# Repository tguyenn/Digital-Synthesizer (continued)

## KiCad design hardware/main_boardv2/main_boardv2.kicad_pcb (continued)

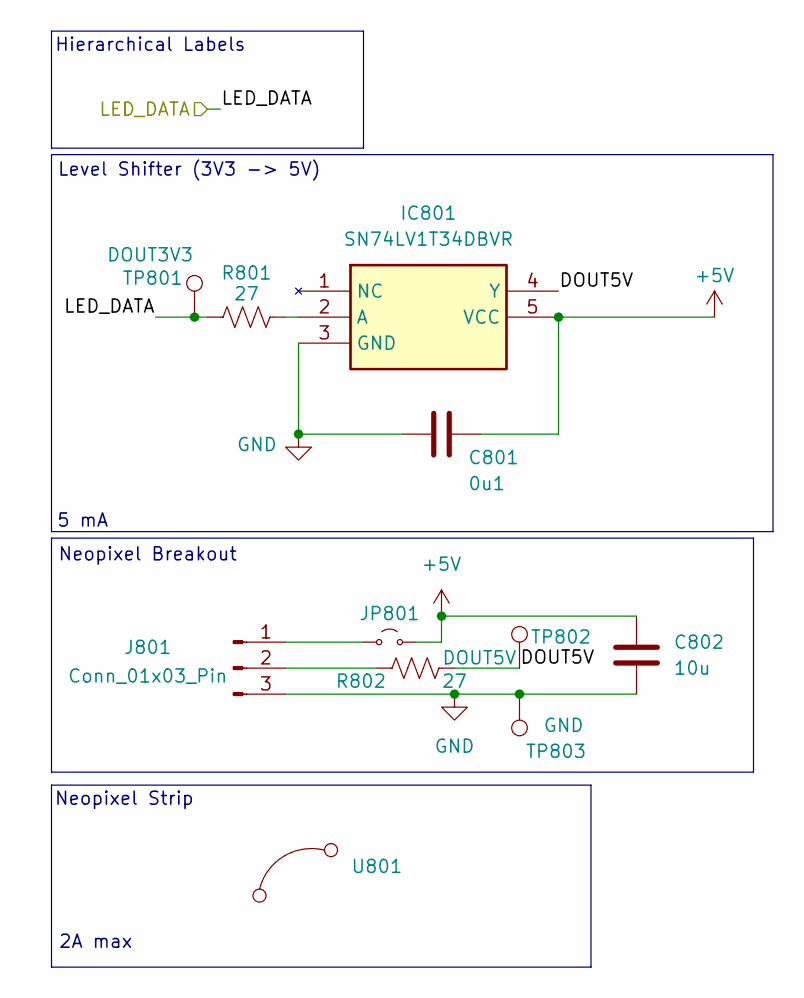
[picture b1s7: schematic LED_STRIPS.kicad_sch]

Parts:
C801: 0u1; C_0603_1608Metric
C802: 10u; C_0603_1608Metric
IC801: SN74LV1T34DBVR; SOT95P280X145-5N; Mouser Part Number 595-SN74LV1T34DBVR
J801: Conn_01x03_Pin; PinHeader_1x03_P2.54mm_Vertical
JP801: Jumper_2_Small_Bridged; SolderJumper-2_P1.3mm_Open_TrianglePad1.0x1.5mm
R801, R802: 27; R_0603_1608Metric
TP801: DOUT3V3; bettertestpoint2
TP802: DOUT5V; bettertestpoint2
TP803: GND; bettertestpoint2
U801: (no value)

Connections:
+5V: C801.2, C802.1, IC801.5 (VCC), JP801.2 (B); also elsewhere on the board
/LED Strip/DOUT5V: IC801.4 (Y), R802.2, TP802.1
/LED Strip/LED_DATA: R801.1, TP801.1; also elsewhere on the board
GND: C801.1, C802.2, IC801.3 (GND), J801.3, TP803.1; also elsewhere on the board
unnamed: IC801.2 (A), R801.2
unnamed: J801.1, JP801.1 (A)
unnamed: J801.2, R802.1

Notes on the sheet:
Neopixel Breakout
5 mA
Neopixel Strip
2A max
Hierarchical Labels
Level Shifter (3V3 -> 5V)

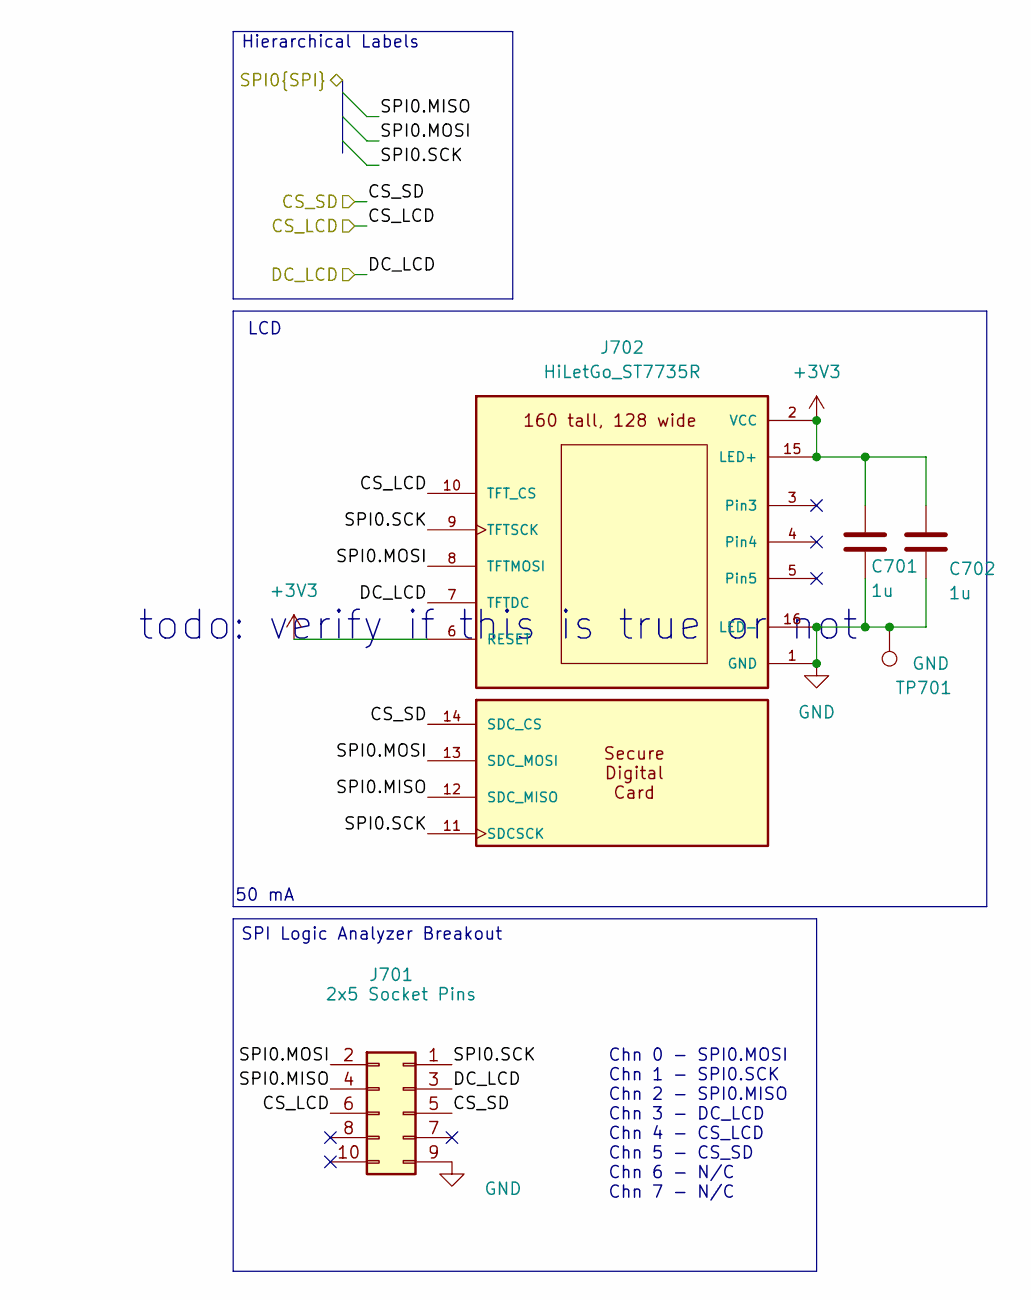
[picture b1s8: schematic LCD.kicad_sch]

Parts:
C701, C702: 1u; C_0603_1608Metric
J701: 2x5 Socket Pins; logic_analyzer_slot_2x5_2.54mm
J702: HiLetGo_ST7735R; hiletgo_st7735r
TP701: GND; bettertestpoint2

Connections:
+3V3: C701.1, C702.1, J702.2 (VCC), J702.6 (RESET), J702.15 (LED+); also elsewhere on the board
/LCD/CS_LCD: J701.6, J702.10 (TFT_CS); also elsewhere on the board
/LCD/CS_SD: J701.5, J702.14 (SDC_CS); also elsewhere on the board
/LCD/DC_LCD: J701.3, J702.7 (TFTDC); also elsewhere on the board
/LCD/SPI0.MISO: J701.4, J702.12 (SDC_MISO); also elsewhere on the board
/LCD/SPI0.MOSI: J701.2, J702.8 (TFTMOSI), J702.13 (SDC_MOSI); also elsewhere on the board
/LCD/SPI0.SCK: J701.1, J702.9 (TFTSCK), J702.11 (SDCSCK); also elsewhere on the board
GND: C701.2, C702.2, J701.9, J702.1 (GND), J702.16 (LED-), TP701.1; also elsewhere on the board

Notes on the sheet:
todo: verify if this is true or not
LCD
SPI Logic Analyzer Breakout
50 mA
Hierarchical Labels
Chn 0 - SPI0.MOSI Chn 1 - SPI0.SCK Chn 2 - SPI0.MISO Chn 3 - DC_LCD Chn 4 - CS_LCD Chn 5 - CS_SD Chn 6 - N/C Chn 7 - N/C

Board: 2 copper layers, 121 parts (0 on the bottom side), 85 nets, no tracks yet.

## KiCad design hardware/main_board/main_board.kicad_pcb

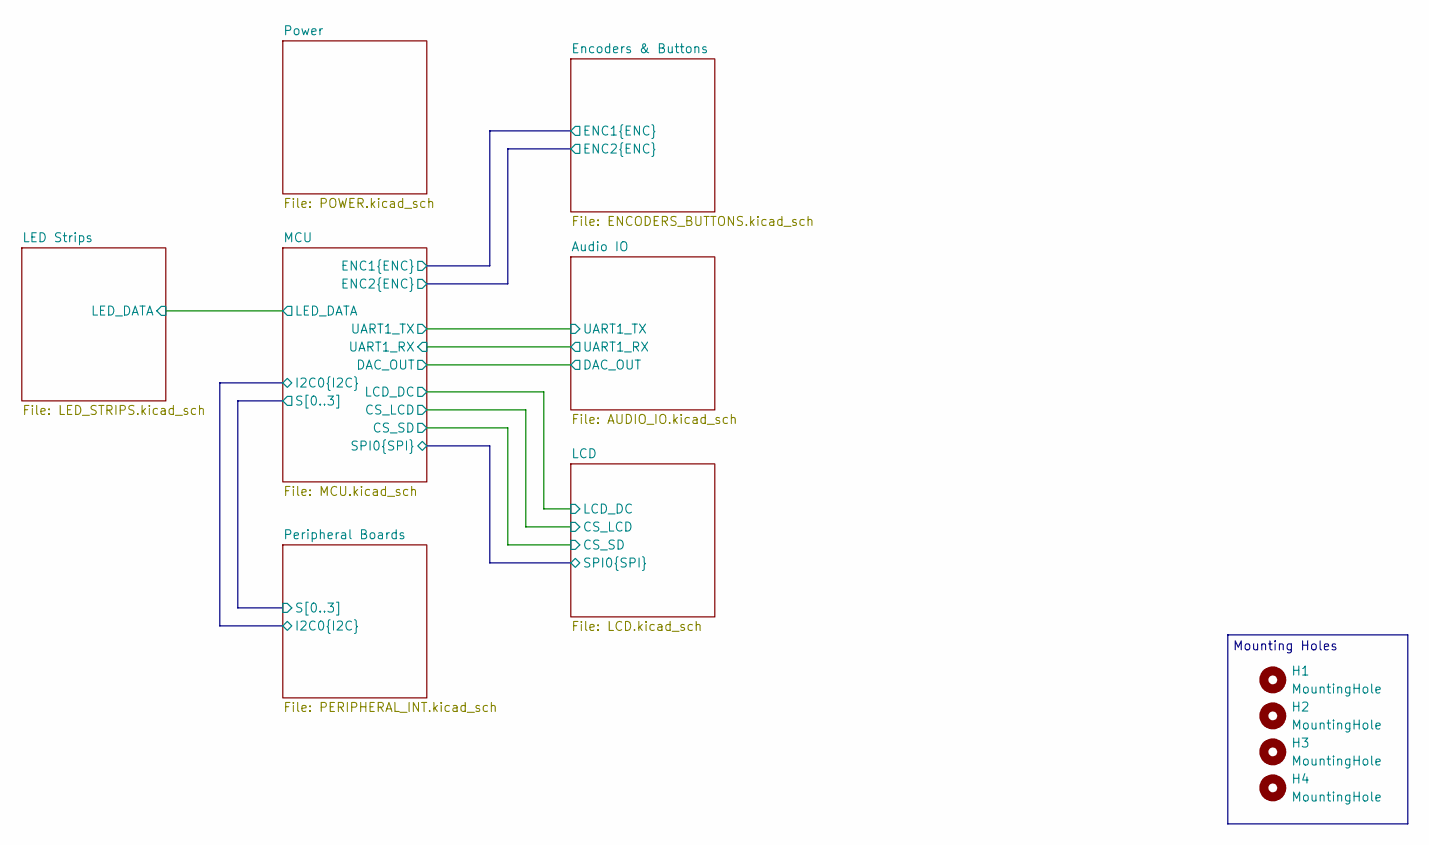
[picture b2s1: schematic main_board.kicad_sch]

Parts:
H1, H2, H3, H4: MountingHole; MountingHole_3.2mm_M3

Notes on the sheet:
Mounting Holes

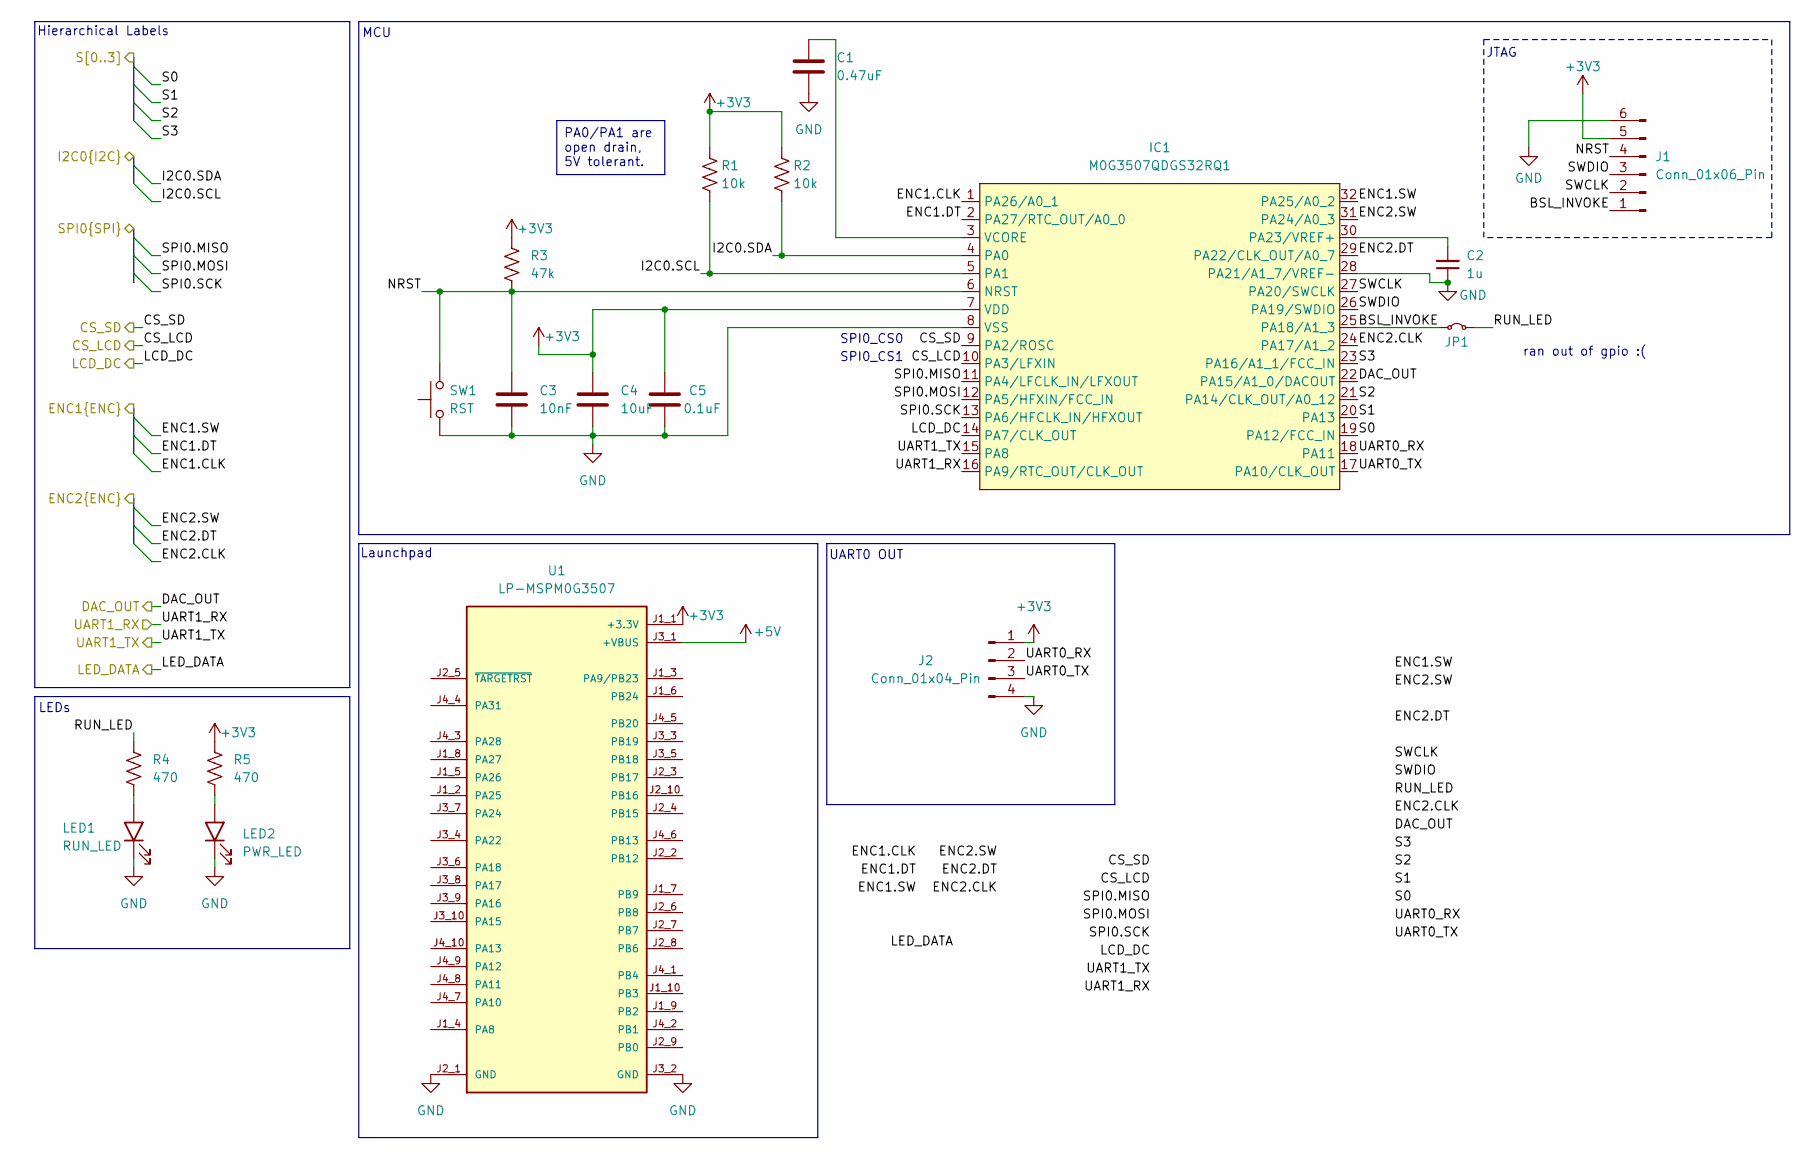
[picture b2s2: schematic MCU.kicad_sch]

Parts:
C1: 0.47uF; C_0805_2012Metric
C2: 1u; C_0805_2012Metric
C3: 10nF; C_0805_2012Metric
C4: 10uF; C_0805_2012Metric
C5: 0.1uF; C_0805_2012Metric
IC1: M0G3507QDGS32RQ1; generic_VSSOP_0.5mm
J1: Conn_01x06_Pin; PinHeader_1x06_P2.54mm_Vertical
J2: Conn_01x04_Pin; PinHeader_1x05_P2.54mm_Vertical
JP1: Jumper_2_Small_Bridged
LED1: RUN_LED; LEDC2012X40N; Mouser Part Number 720-LSR976-NR-1
LED2: PWR_LED; LEDC2012X40N; Mouser Part Number 720-LSR976-NR-1
R1, R2: 10k; R_0805_2012Metric
R3: 47k; R_0805_2012Metric
R4, R5: 470; R_0805_2012Metric
SW1: RST; SW_PUSH_6mm
U1: LP-MSPM0G3507; ti_LP_MSPM0G3507

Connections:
+3V3: C4.1, C5.1, IC1.7 (VDD), J1.5, J2.1, R1.2, R2.2, R3.1, R5.1, U1.J1_1 (+3.3V); also elsewhere on the board
+5V: U1.J3_1 (+VBUS); also elsewhere on the board
/Audio IO/DAC_OUT: IC1.22 (PA15/A1_0/DACOUT); also elsewhere on the board
/Audio IO/UART1_RX: IC1.16 (PA9/RTC_OUT/CLK_OUT); also elsewhere on the board
/Audio IO/UART1_TX: IC1.15 (PA8); also elsewhere on the board
/Encoders & Buttons/ENC1.CLK: IC1.1 (PA26/A0_1); also elsewhere on the board
/Encoders & Buttons/ENC1.DT: IC1.2 (PA27/RTC_OUT/A0_0); also elsewhere on the board
/Encoders & Buttons/ENC1.SW: IC1.32 (PA25/A0_2); also elsewhere on the board
/Encoders & Buttons/ENC2.CLK: IC1.24 (PA17/A1_2); also elsewhere on the board
/Encoders & Buttons/ENC2.DT: IC1.29 (PA22/CLK_OUT/A0_7); also elsewhere on the board
/Encoders & Buttons/ENC2.SW: IC1.31 (PA24/A0_3); also elsewhere on the board
/LCD/CS_LCD: IC1.10 (PA3/LFXIN); also elsewhere on the board
/LCD/CS_SD: IC1.9 (PA2/ROSC); also elsewhere on the board
/LCD/LCD_DC: IC1.14 (PA7/CLK_OUT); also elsewhere on the board
/LCD/SPI0.MISO: IC1.11 (PA4/LFCLK_IN/LFXOUT); also elsewhere on the board
/LCD/SPI0.MOSI: IC1.12 (PA5/HFXIN/FCC_IN); also elsewhere on the board
/LCD/SPI0.SCK: IC1.13 (PA6/HFCLK_IN/HFXOUT); also elsewhere on the board
/MCU/BSL_INVOKE: IC1.25 (PA18/A1_3), J1.1, JP1.1 (A)
/MCU/I2C0.SCL: IC1.5 (PA1), R1.1; also elsewhere on the board
/MCU/I2C0.SDA: IC1.4 (PA0), R2.1; also elsewhere on the board
/MCU/NRST: C3.1, IC1.6 (NRST), J1.4, R3.2, SW1.2
/MCU/RUN_LED: JP1.2 (B), R4.1
/MCU/S0: IC1.19 (PA12/FCC_IN); also elsewhere on the board
/MCU/S1: IC1.20 (PA13); also elsewhere on the board
/MCU/S2: IC1.21 (PA14/CLK_OUT/A0_12); also elsewhere on the board
/MCU/S3: IC1.23 (PA16/A1_1/FCC_IN); also elsewhere on the board
/MCU/SWCLK: IC1.27 (PA20/SWCLK), J1.2
/MCU/SWDIO: IC1.26 (PA19/SWDIO), J1.3
/MCU/UART0_RX: IC1.18 (PA11), J2.2
/MCU/UART0_TX: IC1.17 (PA10/CLK_OUT), J2.3
GND: C1.2, C2.1, C3.2, C4.2, C5.2, IC1.8 (VSS), IC1.28 (PA21/A1_7/VREF-), J1.6, J2.4, LED1.1 (K), LED2.1 (K), SW1.1, U1.J2_1 (GND), U1.J3_2 (GND); also elsewhere on the board
unnamed: C2.2, IC1.30 (PA23/VREF+)
unnamed: C1.1, IC1.3 (VCORE)
unnamed: LED1.2 (A), R4.2
unnamed: LED2.2 (A), R5.2

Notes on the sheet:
MCU
LEDs
UART0 OUT
Launchpad
SPI0_CS1
Hierarchical Labels
SPI0_CS0
ran out of gpio :(
JTAG
PA0/PA1 are open drain, 5V tolerant.

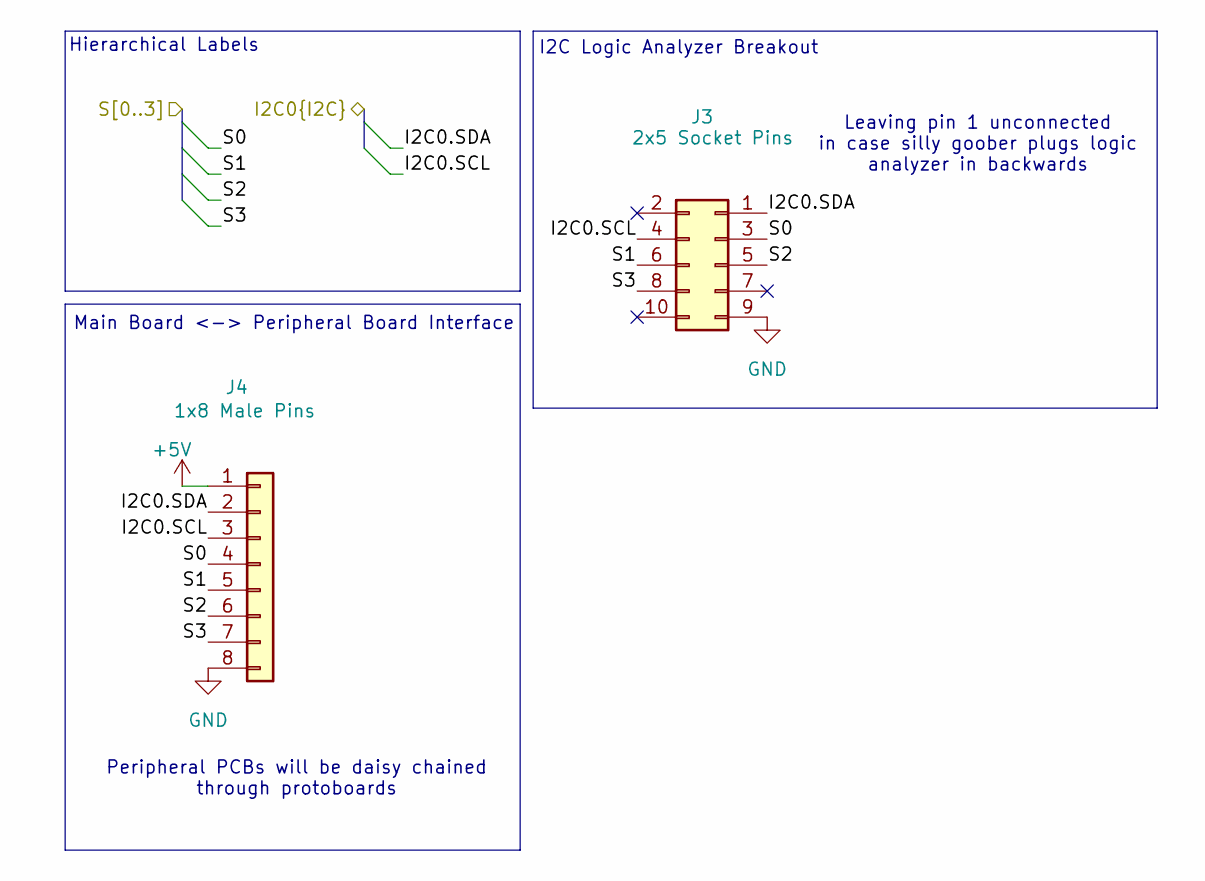
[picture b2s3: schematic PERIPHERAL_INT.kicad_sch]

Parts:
J3: 2x5 Socket Pins; logic_analyzer_slot_2x5_2.54mm
J4: 1x8 Male Pins; PinSocket_1x08_P2.54mm_Vertical

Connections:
+5V: J4.1; also elsewhere on the board
/MCU/I2C0.SCL: J3.4, J4.3; also elsewhere on the board
/MCU/I2C0.SDA: J3.1, J4.2; also elsewhere on the board
/MCU/S0: J3.3, J4.4; also elsewhere on the board
/MCU/S1: J3.6, J4.5; also elsewhere on the board
/MCU/S2: J3.5, J4.6; also elsewhere on the board
/MCU/S3: J3.8, J4.7; also elsewhere on the board
GND: J3.9, J4.8; also elsewhere on the board

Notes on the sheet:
Hierarchical Labels
Peripheral PCBs will be daisy chained through protoboards
Leaving pin 1 unconnected in case silly goober plugs logic analyzer in backwards
Main Board <-> Peripheral Board Interface
I2C Logic Analyzer Breakout

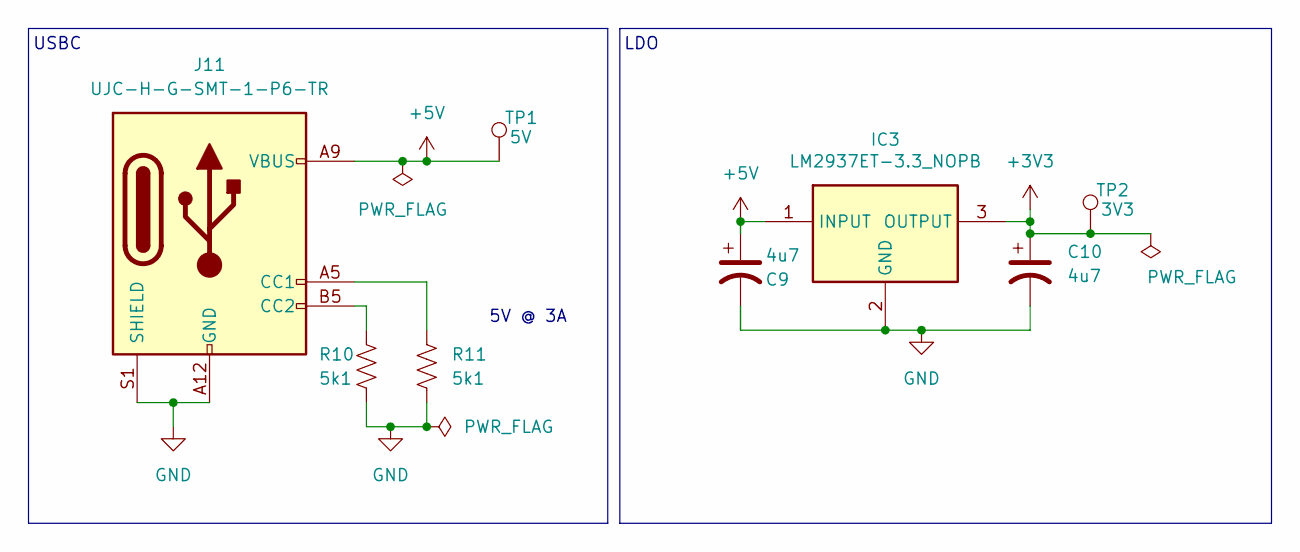
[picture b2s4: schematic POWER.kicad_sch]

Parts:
C9, C10: 4u7; CP_Radial_Tantal200mil
IC3: LM2937ET-3.3_NOPB; TO254P470X1028X1955-3P; Mouser Part Number 926-LM2937ET-3.3NOPB
J11: UJC-H-G-SMT-1-P6-TR; UJCHGSMT1P6TR; Manufacturer_Part_Number UJC-H-G-SMT-1-P6-TR
R10, R11: 5k1; R_0805_2012Metric
TP1: 5V; bettertestpoint2
TP2: 3V3; bettertestpoint2

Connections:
+3V3: C10.1, IC3.3 (OUTPUT), TP2.1; also elsewhere on the board
+5V: C9.1, IC3.1 (INPUT), J11.A9 (VBUS), J11.B9 (VBUS), TP1.1; also elsewhere on the board
GND: C9.2, C10.2, IC3.2 (GND), J11.A12 (GND), J11.B12 (GND), J11.S1 (SHIELD), R10.2, R11.2; also elsewhere on the board
unnamed: J11.A5 (CC1), R11.1
unnamed: J11.B5 (CC2), R10.1

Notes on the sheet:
USBC
LDO
5V @ 3A

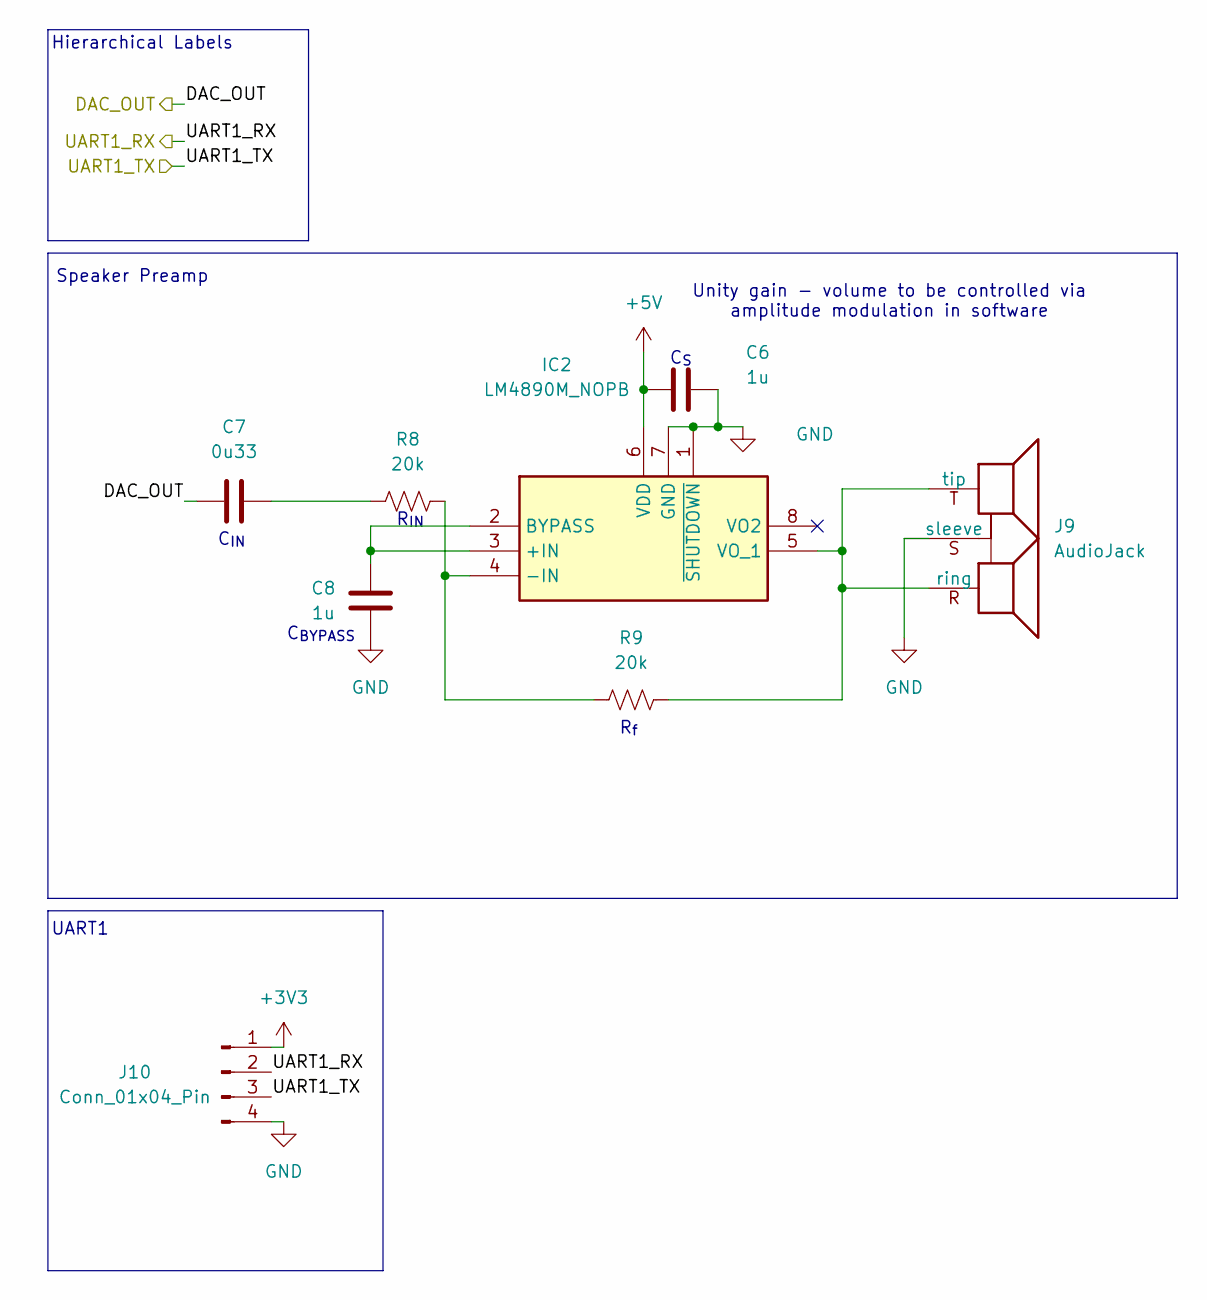
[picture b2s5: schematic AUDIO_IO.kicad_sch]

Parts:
C6, C8: 1u; C_0805_2012Metric
C7: 0u33; C_0805_2012Metric
IC2: LM4890M_NOPB; ti_LM4890M_NOPB; Mouser Part Number 926-LM4890M/NOPB
J9: AudioJack; Jack_3.5mm_CUI_SJ1-3523N_Horizontal
J10: Conn_01x04_Pin; PinHeader_1x05_P2.54mm_Vertical
R8, R9: 20k; R_0805_2012Metric

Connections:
+3V3: J10.1; also elsewhere on the board
+5V: C6.2, IC2.6 (VDD); also elsewhere on the board
/Audio IO/DAC_OUT: C7.1; also elsewhere on the board
/Audio IO/UART1_RX: J10.2; also elsewhere on the board
/Audio IO/UART1_TX: J10.3; also elsewhere on the board
GND: C6.1, C8.2, IC2.1 (~SHUTDOWN), IC2.7 (GND), J9.S (sleeve), J10.4; also elsewhere on the board
unnamed: C7.2, R8.1
unnamed: C8.1, IC2.2 (BYPASS), IC2.3 (+IN)
unnamed: IC2.4 (-IN), R8.2, R9.1
unnamed: IC2.5 (VO_1), J9.R (ring), J9.T (tip), R9.2

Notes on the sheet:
Unity gain - volume to be controlled via amplitude modulation in software
Speaker Preamp
UART1
R_{f}
C_{BYPASS}
R_{IN}
C_{S}
C_{IN}
Hierarchical Labels

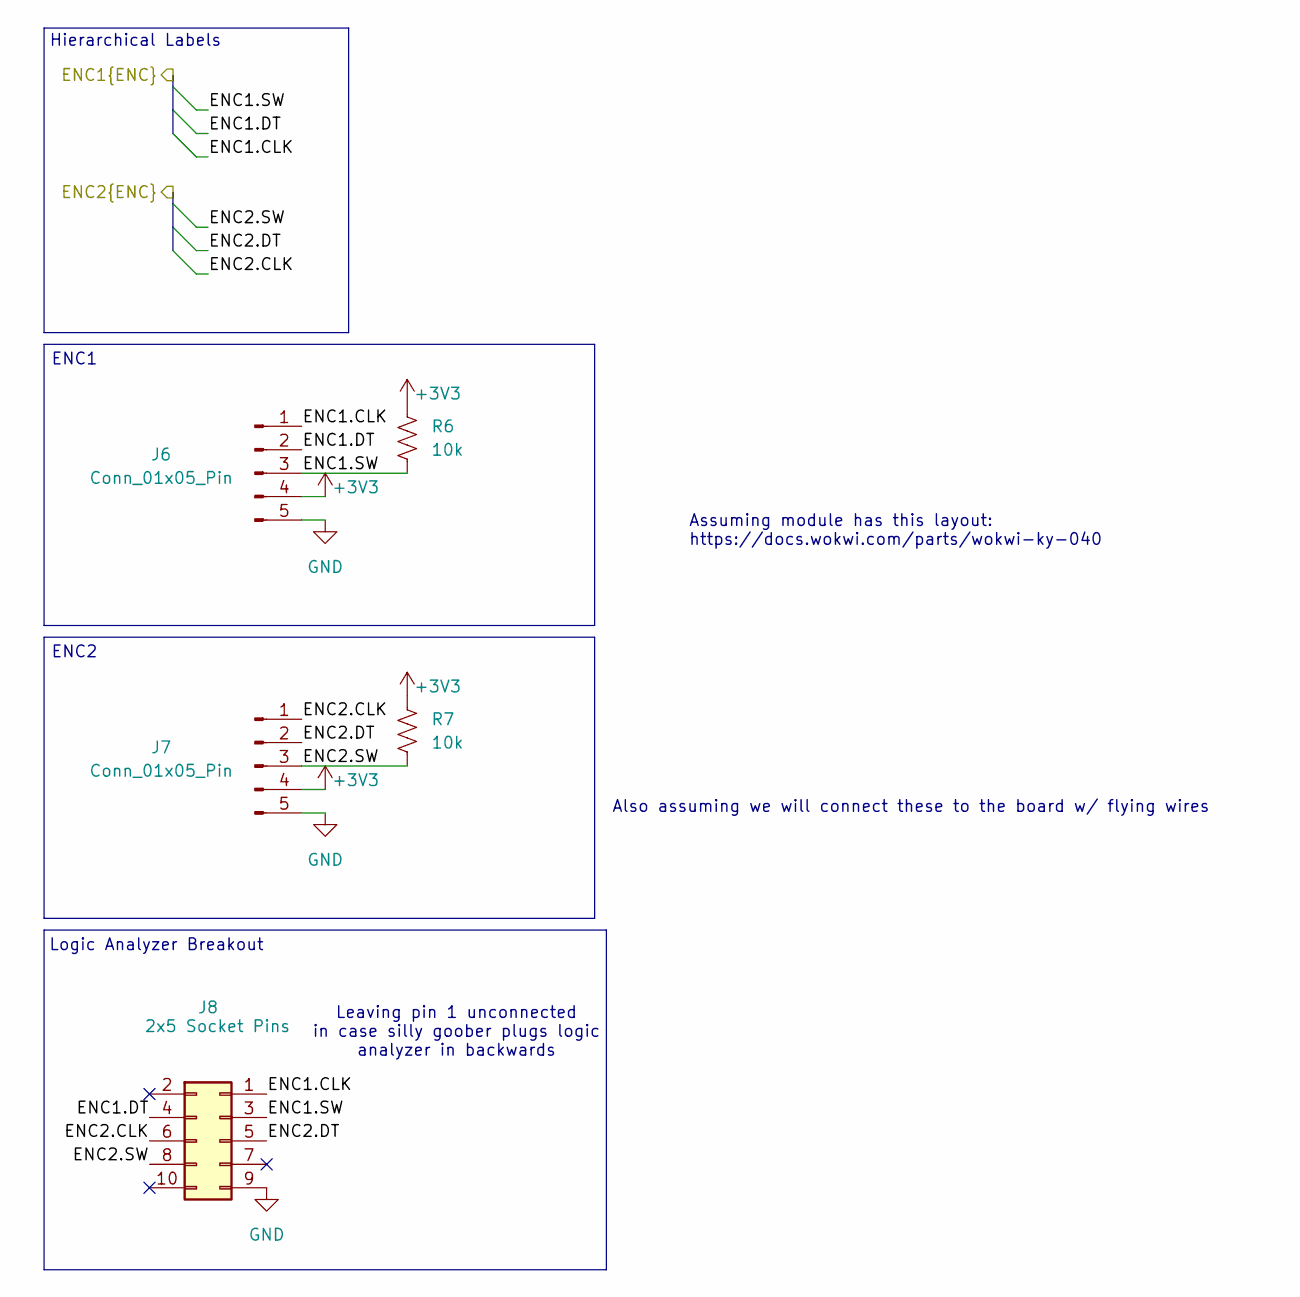
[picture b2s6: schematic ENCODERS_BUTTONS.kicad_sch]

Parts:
J6, J7: Conn_01x05_Pin; PinHeader_1x05_P2.54mm_Vertical
J8: 2x5 Socket Pins; logic_analyzer_slot_2x5_2.54mm
R6, R7: 10k; R_0805_2012Metric

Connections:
+3V3: J6.4, J7.4, R6.2, R7.2; also elsewhere on the board
/Encoders & Buttons/ENC1.CLK: J6.1, J8.1; also elsewhere on the board
/Encoders & Buttons/ENC1.DT: J6.2, J8.4; also elsewhere on the board
/Encoders & Buttons/ENC1.SW: J6.3, J8.3, R6.1; also elsewhere on the board
/Encoders & Buttons/ENC2.CLK: J7.1, J8.6; also elsewhere on the board
/Encoders & Buttons/ENC2.DT: J7.2, J8.5; also elsewhere on the board
/Encoders & Buttons/ENC2.SW: J7.3, J8.8, R7.1; also elsewhere on the board
GND: J6.5, J7.5, J8.9; also elsewhere on the board

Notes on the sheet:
Also assuming we will connect these to the board w/ flying wires
Logic Analyzer Breakout
ENC1
ENC2
Leaving pin 1 unconnected in case silly goober plugs logic analyzer in backwards
Hierarchical Labels
Assuming module has this layout: https://docs.wokwi.com/parts/wokwi-ky-040

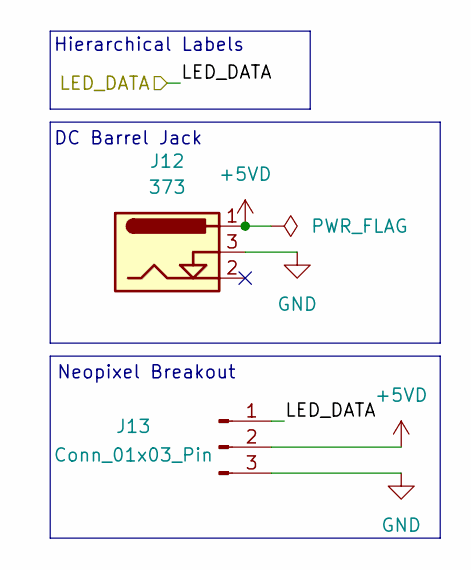
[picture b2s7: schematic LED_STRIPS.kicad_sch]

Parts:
J12: 373; Mouser Part Number 485-373
J13: Conn_01x03_Pin; PinHeader_1x03_P2.54mm_Vertical

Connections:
+5VD: J12.1, J13.2
/LED Strips/LED_DATA: J13.1
GND: J12.3, J13.3; also elsewhere on the board

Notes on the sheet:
Neopixel Breakout
DC Barrel Jack
Hierarchical Labels

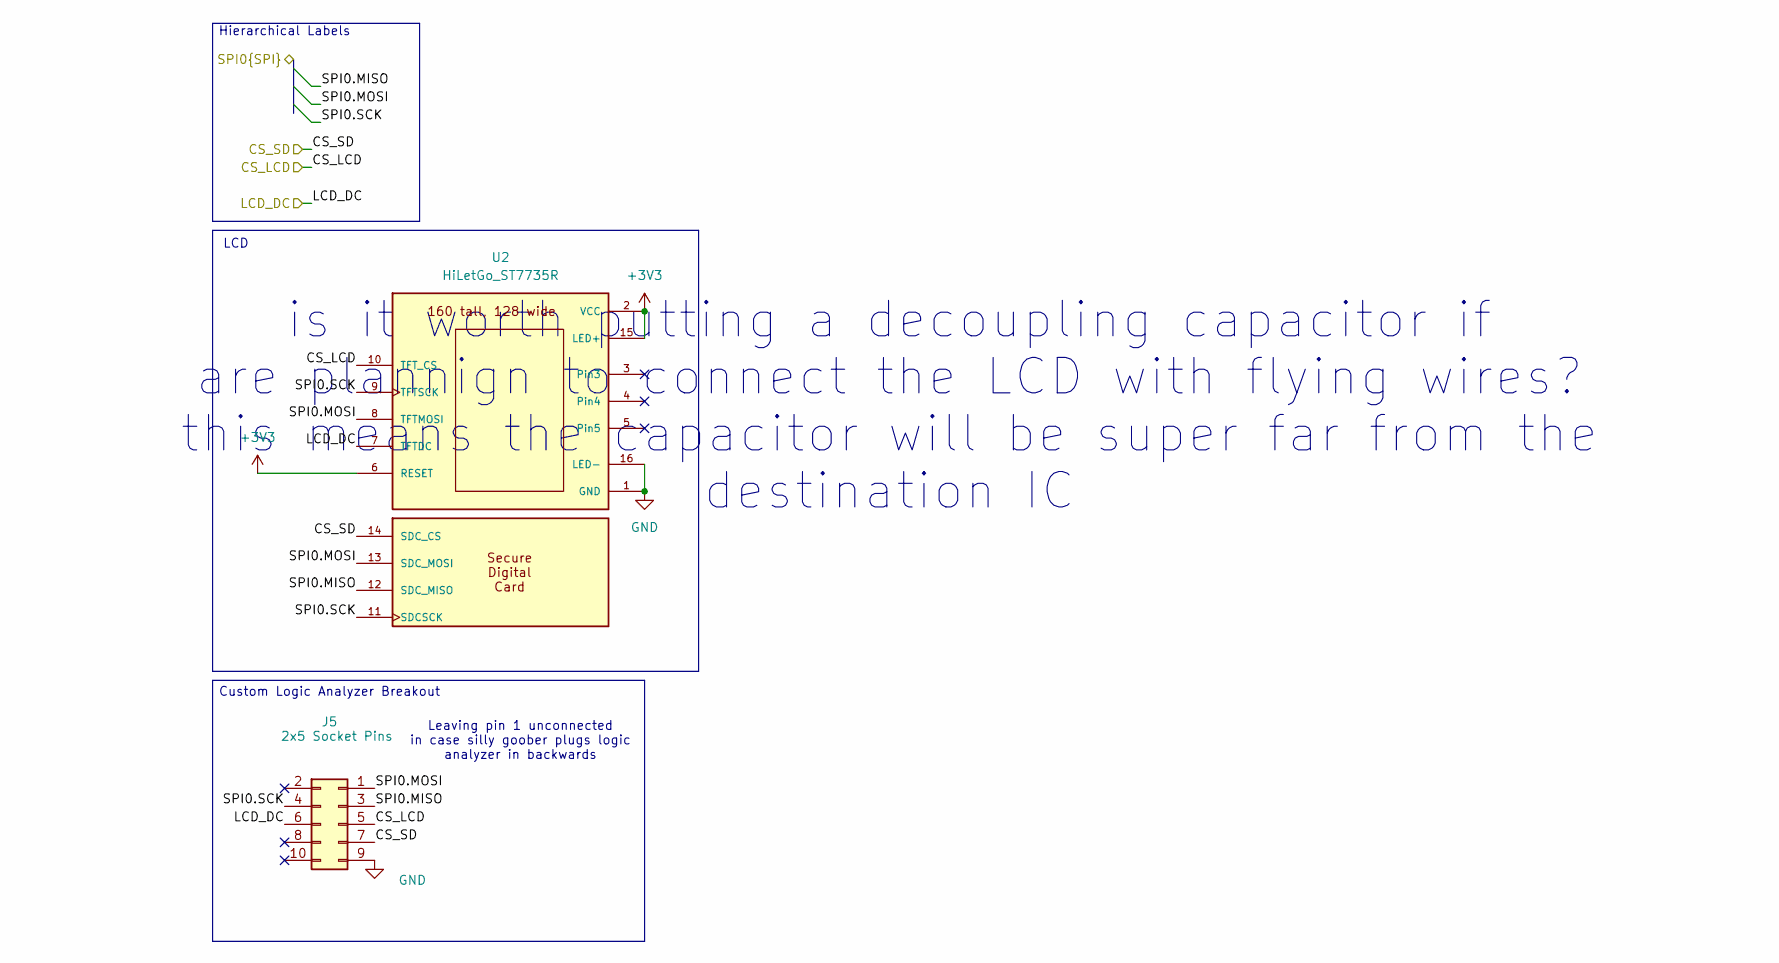
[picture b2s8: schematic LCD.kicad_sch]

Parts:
J5: 2x5 Socket Pins; logic_analyzer_slot_2x5_2.54mm
U2: HiLetGo_ST7735R; hiletgo_st7735r

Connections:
+3V3: U2.2 (VCC), U2.6 (RESET), U2.15 (LED+); also elsewhere on the board
/LCD/CS_LCD: J5.5, U2.10 (TFT_CS); also elsewhere on the board
/LCD/CS_SD: J5.7, U2.14 (SDC_CS); also elsewhere on the board
/LCD/LCD_DC: J5.6, U2.7 (TFTDC); also elsewhere on the board
/LCD/SPI0.MISO: J5.3, U2.12 (SDC_MISO); also elsewhere on the board
/LCD/SPI0.MOSI: J5.1, U2.8 (TFTMOSI), U2.13 (SDC_MOSI); also elsewhere on the board
/LCD/SPI0.SCK: J5.4, U2.9 (TFTSCK), U2.11 (SDCSCK); also elsewhere on the board
GND: J5.9, U2.1 (GND), U2.16 (LED-); also elsewhere on the board

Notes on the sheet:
LCD
Custom Logic Analyzer Breakout
Hierarchical Labels
Leaving pin 1 unconnected in case silly goober plugs logic analyzer in backwards
is it worth putting a decoupling capacitor if are plannign to connect the LCD with flying wires? this means the capacitor will be super far from the destination IC

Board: 2 copper layers, 48 parts (0 on the bottom side), 41 nets, no tracks yet.

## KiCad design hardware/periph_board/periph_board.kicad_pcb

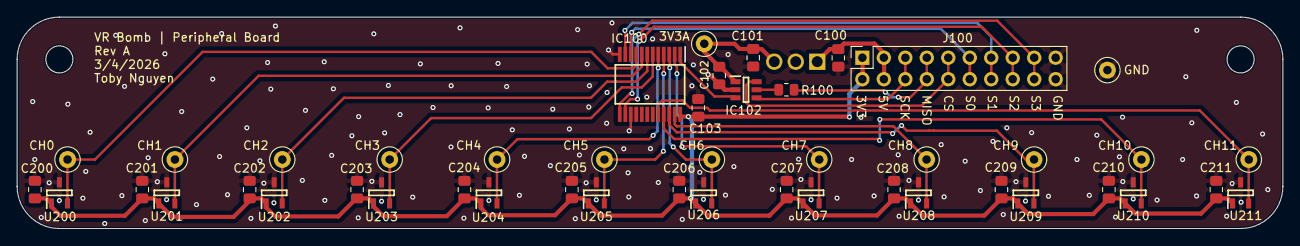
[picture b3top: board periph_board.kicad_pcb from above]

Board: 2 copper layers, 149.7 x 25.0 mm, 49 parts (1 on the bottom side), 25 nets.

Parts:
C100, C101, C102, C103, C200, C201, C202, C203, C204, C205, C206, C207, C208, C209, C210, C211: 1u; C_0805_2012Metric_Pad1.18x1.45mm_HandSolder
H100, H101: MountingHole; MountingHole_3.2mm_M3
IC100: CD74HC4067SM96; SOP65P780X200-24N
IC101: LM2937ET-3.3_NOPB; TO254P470X1028X1955-3P
IC102: ADC121S021CIMFX_NOPB; SOT95P280X145-6N
J100: 2x10 Male Pins; PinSocket_2x10_P2.54mm_Vertical
R100: 100; R_0805_2012Metric
TP100: CH0; bettertestpoint2
TP102: CH1; bettertestpoint2
TP103: 3V3A; bettertestpoint2
TP105: CH2; bettertestpoint2
TP106: CH3; bettertestpoint2
TP107: CH4; bettertestpoint2
TP108: CH5; bettertestpoint2
TP109: CH6; bettertestpoint2
TP110: GND; bettertestpoint2
TP111: CH7; bettertestpoint2
TP112: CH8; bettertestpoint2
TP113: CH9; bettertestpoint2
TP114: CH10; bettertestpoint2
TP115: CH11; bettertestpoint2
U200, U201, U202, U203, U204, U205, U206, U207, U208, U209, U210, U211: AH49HNTR-G1; SOT95P282X145-3N

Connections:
+3.3VADC: C101.2, C102.2, IC101.3 (OUTPUT), IC102.1 (VA), TP103.1
+3V3: C103.2, C200.2, C201.2, C202.2, C203.2, C204.2, C205.2, C206.2, C207.2, C208.2, C209.2, C210.2, C211.2, IC100.24 (VCC), J100.1, J100.2, U200.1 (VCC), U201.1 (VCC), U202.1 (VCC), U203.1 (VCC), U204.1 (VCC), U205.1 (VCC), U206.1 (VCC), U207.1 (VCC), U208.1 (VCC), U209.1 (VCC), U210.1 (VCC), U211.1 (VCC)
+5V: C100.2, IC101.1 (INPUT), J100.3, J100.4
/CH0: IC100.9 (I0), TP100.1, U200.2 (OUT)
/CH1: IC100.8 (I1), TP102.1, U201.2 (OUT)
/CH2: IC100.7 (I2), TP105.1, U202.2 (OUT)
/CH3: IC100.6 (I3), TP106.1, U203.2 (OUT)
/CH4: IC100.5 (I4), TP107.1, U204.2 (OUT)
/CH5: IC100.4 (I5), TP108.1, U205.2 (OUT)
/CH6: IC100.3 (I6), TP109.1, U206.2 (OUT)
/CH7: IC100.2 (I7), TP111.1, U207.2 (OUT)
/CH8: IC100.23 (I8), TP112.1, U208.2 (OUT)
/CH9: IC100.22 (I9), TP113.1, U209.2 (OUT)
/CH10: IC100.21 (I10), TP114.1, U210.2 (OUT)
/CH11: IC100.20 (I11), TP115.1, U211.2 (OUT)
/CS: IC102.6 (CS), J100.9, J100.10
/HALL_OUT: IC100.1 (COMMON_INPUT/OUTPUT), IC102.3 (VIN)
/MISO: J100.7, J100.8, R100.2
/S0: IC100.10 (S0), J100.11, J100.12
/S1: IC100.11 (S1), J100.13, J100.14
/S2: IC100.14 (S2), J100.15, J100.16
/S3: IC100.13 (S3), J100.17, J100.18
/SCK: IC102.4 (SCLK), J100.5, J100.6
GND: C100.1, C101.1, C102.1, C103.1, C200.1, C201.1, C202.1, C203.1, C204.1, C205.1, C206.1, C207.1, C208.1, C209.1, C210.1, C211.1, IC100.12 (GND), IC100.15 (~E), IC101.2 (GND), IC102.2 (GND), J100.19, J100.20, TP110.1, U200.3 (GND), U201.3 (GND), U202.3 (GND), U203.3 (GND), U204.3 (GND), U205.3 (GND), U206.3 (GND), U207.3 (GND), U208.3 (GND), U209.3 (GND), U210.3 (GND), U211.3 (GND)
unnamed: IC102.5 (SDATA), R100.1

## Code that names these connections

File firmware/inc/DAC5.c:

/* DAC5.c
 * Students put your names here
 * Modified: put date here
 * 5-bit binary-weighted DAC connected to PB4-PB0
 */
#include <ti/devices/msp/msp.h>
#define PB0INDEX  11 // UART0_TX  SPI1_CS2  TIMA1_C0  TIMA0_C2
#define PB1INDEX  12 // UART0_RX  SPI1_CS3  TIMA1_C1  TIMA0_C2N
#define PB2INDEX  14 // UART3_TX  UART2_CTS I2C1_SCL  TIMA0_C3  UART1_CTS TIMG6_C0  TIMA1_C0
#define PB3INDEX  15 // UART3_RX  UART2_RTS I2C1_SDA  TIMA0_C3N UART1_RTS TIMG6_C1  TIMA1_C1
#define PB4INDEX  16 // UART1_TX  UART3_CTS TIMA1_C0  TIMA0_C2  TIMA1_C0N

// **************DAC5_Init*********************
// Initialize 5-bit DAC, called once
// Input: none
// Output: none
void DAC5_Init(void){
// Assumes LaunchPad_Init has been called
// I.e., PortB has already been reset and activated (do not reset PortB here again)
     // write this
}

// **************DAC5_Out*********************
// output to DAC5
// Input: 5-bit data, 0 to 31
// Input=n is converted to n*3.3V/31
// Output: none
// Note: this solution must be friendly
void DAC5_Out(uint32_t data){
     // write this
}

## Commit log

2026-02-28 Flatten
2026-03-03 added drawio file. added samacsys config for both kicad projects
2026-03-03 sw gitignore
2026-03-04 Finished Rev A of peripheral PCB schematic/layout (need to find values for resistors lol). Added ECE445L lab docs
2026-03-05 layout with bad adc
2026-03-06 MSPM0 Starter
2026-03-07 ece445l libraries added. moved mspm0 starter to /hw to /hardware with other files
2026-03-07 third peripheral board layout done
2026-03-07 replaced LDO thing to be free one in lab checkout. added some stuff to main board (wip)
2026-03-08 finished periph board rev A. ready for order! added some more content to main board
2026-03-13 pls review pboard with i2c sensor
2026-03-17 Fixed DRC errors
2026-03-17 Created gerbers using kicad-jlcpcb-tools
2026-03-23 added 319k lab 7 to resources
2026-03-23 please
2026-03-23 fixed peripheral board dimensions to be compatible with 2.54 mm pitch protoboard for daisy chaining. deleted gerbers. added some more content to main board (wip)
2026-03-23 Jeffey try building this
2026-03-25 reorganize lol
2026-03-26 added lakshay suggestions to peripheral board. removed bypass jumper from main board audio amp. added led strip interface. added too many things to remember i forgor
2026-03-27 main board stuff. removed usbc for power. added level shifter for led logic signal. added lights for mux select signals. finished layout + pass DRC
2026-03-27 removed starter msp proj. fixed all 3d model paths (hopefully). added power led and changed MH to be 319k standoff compatible
2026-03-27 added requirements doc
2026-03-28 pcb review changes
2026-03-30 added selection line LEDs to p board
2026-03-30 Dimensioned correctly, need to reroute for hall effects
2026-03-30 Rerouted for adjusted key offsets
2026-03-31 changed level shifter. bunch of aesthetic changes. led resistors changed on main board. saving before nuke mouser.co.uk
2026-03-31 finished everything except bom information. drc verification
2026-03-31 fuck shit
2026-04-03 updated requirements doc
2026-04-09 led info
2026-04-09 up to date scheamtic
2026-04-14 build and flash blinky to launchpad in mainboard project dir
2026-04-16 led chaser launchpad select lines
2026-04-17 rip morris code lmao
2026-04-18 Added launchpad/chip switch, switched main
2026-04-18 wip led strip
2026-04-18 kys harddare
2026-04-18 added ti driver files for dma
2026-04-19 moved dma to its own file
2026-04-19 i2c?
2026-04-20 i2c and adc sampling working
2026-04-20 working ADC for all 60 keys
2026-04-20 spi. butchered main
2026-04-20 Modified SPI.c, REMOVED RESET PIN
2026-04-21 Previous commit broken? SPI.c with no reset
2026-04-21 Added DMA stuff currently working on
2026-04-21 Now linking whole lib folder, partially working DMA stuff
2026-04-21 fixed encoder init
2026-04-22 encoder and switch interrupt working
2026-04-22 Pingpong using driverlib works
2026-04-22 cleaned up main. please no more merge conflict. also added some dma stuff
2026-04-22 Starting timer control of DAC
2026-04-23 DMA and DAC working without driverlib
2026-04-23 working encoder and display
2026-04-23 Attack and release framework working
2026-04-23 fixed graphics stuff
2026-04-23 Beginning integration
2026-04-23 Basic universal thresholds working
2026-04-23 basic enveloping
2026-04-24 enveloping
2026-04-25 cleaned
2026-04-28 rev2 coming soon ™️
2026-04-29 docs test
2026-04-29 gitattributes + image render test
2026-04-29 wrote most of electrical docs. picture test!
2026-04-29 Update README with video upload
2026-04-29 more readme i go bed
2026-04-29 asdasd
2026-04-29 color test
2026-04-30 new hardware
2026-05-01 wired most of new hardware. need to reviist audio stuff
2026-05-01 Change video source link in README
    Updated video source link in README for project demonstration.
2026-05-01 changed caption
2026-05-01 more readme. added electrical design content and fixed drawio diagrams
2026-05-03 more readme
2026-05-03 bruh
2026-05-03 more hardware
2026-05-14 readme
2026-05-16 dubious hardware schematic 'done'. need to go back and revise passives and verify IC connections, esp the DAC. modified readme
2026-05-16 long pcb image
2026-06-12 schematic sorta done? resized all RC packages to 0805
2026-06-18 resized all package to 0603
